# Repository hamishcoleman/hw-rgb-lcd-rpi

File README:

This design is to adapt a "raw" or "dotclock" LCD to the Raspberry-Pi
expansion pinout, and allow it to be connected directly to the GPU
(not via SPI)

TODO:
- clarify the OSHW licence
- Add more documentation
- The lq043t1dg03 footprint needs adjusting - the large mechanical stay
  pads are in the wrong places
- All the custom footprints need a pin 1 indicator

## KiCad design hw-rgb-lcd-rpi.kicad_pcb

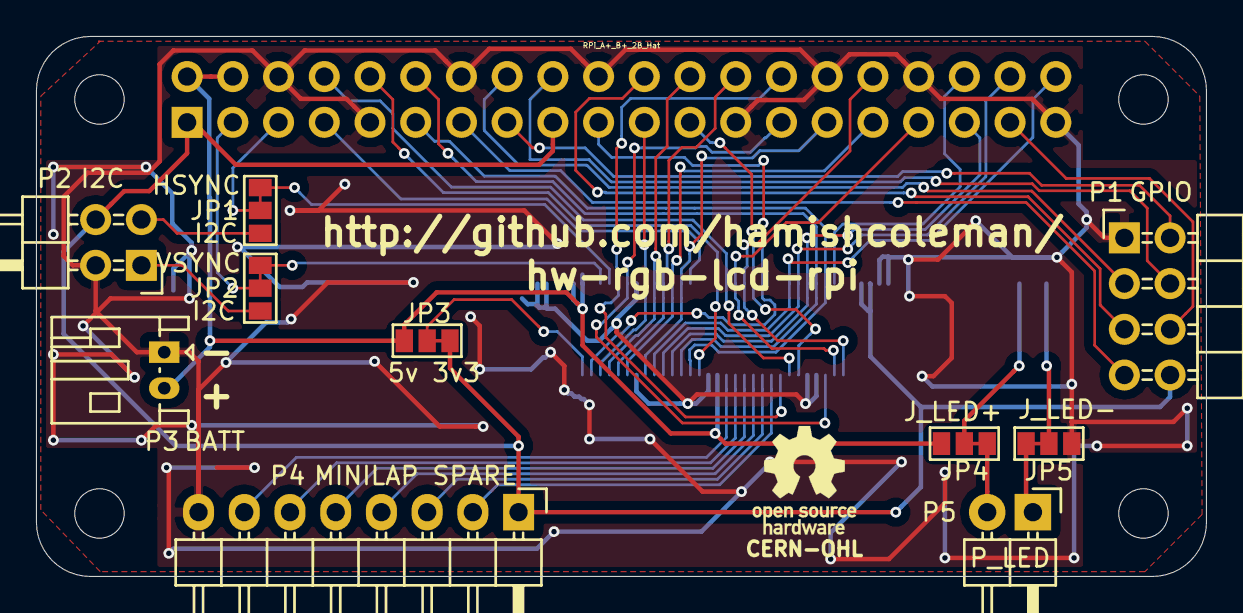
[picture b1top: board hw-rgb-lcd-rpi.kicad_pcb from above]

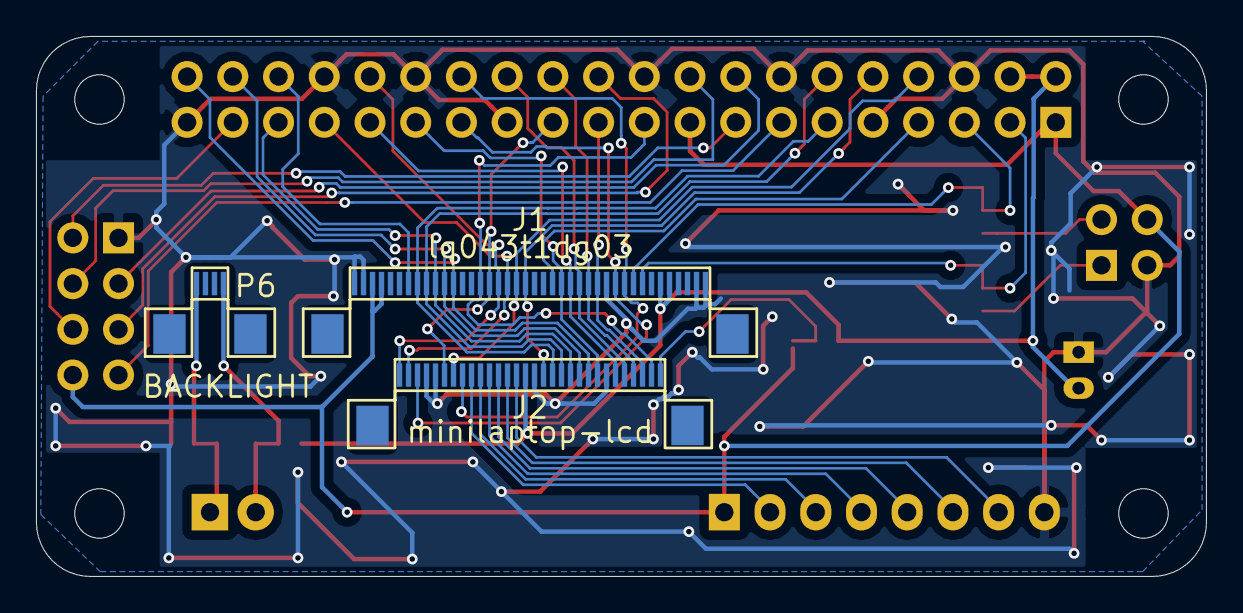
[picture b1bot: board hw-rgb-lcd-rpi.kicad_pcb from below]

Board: 2 copper layers, 65.0 x 30.0 mm, 14 parts (3 on the bottom side), 42 nets.

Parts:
J1: lq043t1dg03; FPC_40
J2: minilaptop-lcd; FPC_30
JP1: HSYNC; GS3
JP2: VSYNC; GS3
JP3: 5v 3v3; GS3
JP4: J_LED+; GS3
JP5: J_LED-; GS3
P1: GPIO; Pin_Header_Angled_2x04
P2: I2C; Pin_Header_Angled_2x02
P3: BATT; JST_PH_S2B-PH-K_02x2.00mm_Angled
P4: MINILAP SPARE; Pin_Header_Angled_1x08
P5: P_LED; Pin_Header_Angled_1x02
P6: BACKLIGHT; FPC_4
U1: RPi_A+_B+_2B_Hat; z_RPiZero_Hat_NPTH

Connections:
+BATT: J1.35, J1.36, J2.15, JP3.1, JP4.3, P3.2, U1.2, U1.4
/B2: J1.23, U1.7
/B3: J1.24, J2.23, U1.29
/B4: J1.25, J2.25, U1.31
/B5: J1.26, J2.26, U1.26
/B6: J1.27, J2.27, U1.24
/B7: J1.28, J2.28, U1.21
/DEN: J1.31, J2.8, U1.28
/DOTCLK: J1.30, J2.3, U1.27
/G2: J1.15, J2.29, U1.19
/G3: J1.16, J2.6, U1.23
/G4: J1.17, J2.1, U1.32
/G5: J1.18, J2.2, U1.33
/G6: J1.19, J2.7, U1.8
/G7: J1.20, J2.17, U1.10
/GPIO22: P1.2, U1.15
/GPIO23: P1.3, U1.16
/GPIO24: P1.4, U1.18
/GPIO25: P1.5, U1.22
/GPIO26: P1.6, U1.37
/GPIO27: P1.7, U1.13
/H_SYNC: J1.32, JP1.2, JP1.3, U1.5
/R2: J1.7, U1.36
/R3: J1.8, J2.18, U1.11
/R4: J1.9, J2.19, U1.12
/R5: J1.10, J2.20, U1.35
/R6: J1.11, J2.21, U1.38
/R7: J1.12, J2.22, U1.40
/SCL: JP1.1, P2.3
/SDA: JP2.3, P2.1
/V_SYNC: J1.33, JP2.1, JP2.2, U1.3
GND: J1.1, J1.2, J1.29, J1.39, J1.40, J2.4, J2.5, J2.16, J2.24, JP5.1, P1.1, P2.2, P3.1, P4.8, U1.6, U1.9, U1.14, U1.20, U1.25, U1.30, U1.34, U1.39
unnamed: J2.9, P4.2
unnamed: J2.10, P4.3
unnamed: J2.11, P4.4
unnamed: J2.12, P4.5
unnamed: J2.13, P4.6
unnamed: J2.14, P4.7
unnamed: J2.30, JP3.2
unnamed: JP4.1, JP4.2, P5.2, P6.4
unnamed: JP5.2, JP5.3, P5.1, P6.1
VCC: J1.3, J1.4, JP3.3, P1.8, P2.4, P4.1, U1.1, U1.17

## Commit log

2016-11-10 Create empty kicad project
2016-11-10 Import Raspberry Pi libraries from kicad forum: https://forum.kicad.info/t/raspberry-pi-b-hat-template/738/35
2016-11-10 Import library to project
2016-11-10 Add new parts for the two LCD connectors
2016-11-10 Add bus wires
2016-11-10 Add gitignore
2016-11-11 Label and allow connections to the HAT I2C pins
2016-11-11 All pins wired up
2016-11-11 Add missing backlight connector
2016-11-11 Add most footprints
2016-11-11 Add some footprints for the FPC connectors
2016-11-11 Add backlight FPC, adjust headers to be smaller
2016-11-11 Ignore pcb backups
2016-11-11 Initial trial placement of all parts
2016-11-11 Set design rules as per hackvana
2016-11-11 Make power tracks visibly wider
2016-11-11 minilaptop power supply should select between powered by VCC or VBATT - fix
2016-11-11 Rearrange I2C pins for simpler layout
2016-11-11 Switch more pins to make layout simpler
2016-11-11 All tracks routed, however the layout is sub-optimal
2016-11-11 Rearrange the mini-laptop spare pins to make routing simple
2016-11-11 Clean up routing
2016-11-11 Minor label adjustments
2016-11-11 Add GND fill
2016-11-11 Ensure keepout areas and edge cuts are marked
2016-11-11 Add labels and adjust silkscreen for all parts
2016-11-11 Add fabrication output handling
2016-11-11 Save gerber settings to project
2016-11-11 Re-add fill regions
2016-11-11 Add dimension lines
2016-11-12 Add NPTH file to gerbv project
2016-11-16 Add README
2016-11-22 Add a licence name to the silkscreen
2016-11-22 update design rules for via sizes after talking to hackvana
2016-11-22 Minor track adjustment - two tracks didnt need to be so close
2016-11-22 Search and replace via drill sizes to match suggestions
2016-11-22 Use gerblook and friends to address copper layer wierdness
2016-11-22 Stitch the copper fills together where it seemed needed, more minor adjustments to remove warts
2016-12-05 Update TODO list with current items
2017-02-13 Add some simple automation to create the gerbers
2018-06-06 Make it clear which licence I have always considered this under

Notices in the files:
hw-rgb-lcd-rpi.kicad_pcb:
CERN-OHL
